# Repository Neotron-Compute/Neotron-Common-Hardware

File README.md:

# Neotron-Common-Hardware

Contains KiCad footprints and symbols shared across multiple Neotron projects. It also contains example schematics for circuits we expect to see on most Neotron boards.

## Components

### Audio Codec

* Texas Instruments TLV320AIC23B
  * I²S + I²C interface
  * Amplified 32mW headphone output and line out
  * Microphone in and line in
  * TSSOP-28 package (0.635mm pitch)
* Triple 3.5mm TRS jack (Kycon STX-4335-5BGP-S1)
  * Headphone Out (green)
  * Line In (blue)
  * Microphone In (pink)
* AC'97 Pin Header
  * Headphone Out
  * Microphone In
* Extra line-level output pin header (e.g. for additional RCA audio jacks - operates in addition to 3.5mm headphone jack output)
* Internal line-level input pin header (e.g. for CD-ROM audio - disabled when line-in 3.5mm jack in-use)

### Super VGA output

* 15-pin D-Sub VGA interface
* 18-bit (6-6-6) and 12-bit (4-4-4) RGB R2R DACs
  * Requires you to connect up a CPU that can generate digital parallel RGB video
* 3peak TPF133A or Texas Instruments THS7316 RGB video buffer
   * 36 MHz bandwidth - 1024x768@60Hz maximum
   * 6dB gain
   * Drives 75 ohm standard VGA interface
   * SOIC-8 package (1.27mm pitch)
* Texas Instruments TPD7S019 Sync/DDC level shifter and RGB EMC filter
   * SSOP-16 package (0.635mm pitch)

### RS232 Interface

* Tx, Rx, RTS and CTS signals
* 3.3V TTL on the MCU side
* Low-power ST ST3232C RS-232 level shifter (powered from single 3.3V rail)
* RS-232 signalling on a 9-pin D-Sub connector (or 10-pin IDC box header), wired DTE

### USB

* Four port USB 2.0 High Speed hub
* MaxLinear XR22404CG28 USB2.0 hub IC
  * SSOP-28 package (0.635mm pitch)
* Two USB 2.0 High Speed Type-A ports
* 8-pin PC case style USB pin-header (providing two USB 2.0 High Speed ports)
* Each port limited to 500mA with over-current protection

### Ethernet

* 10/100base-T Ethernet
* Microchip ENC424J600 Ethernet MAC/PHY with SPI connection to main CPU
  * TQFP-44 package (0.8mm pitch)
* Link and Activity LEDs

### Board Management Controller

Power-on Reset sequencing, soft shutdown, voltage monitoring and PS/2 interfacing is handled by a separate STM32F0 SoC.

* ST Micro STM32F0 (STM32F030K6T6) microcontroller
  * 32-bit Arm Cortex-M0+ Core
  * 3.3V I/O (5V tolerant)
  * 32 KiB Flash
  * 4 KiB SRAM
  * LQFP-32 package (0.8mm pitch)
* Controls two PS/2 ports
* Monitors 5V and 3.3V rails
* Controls system reset, soft-on and soft-off for main CPU
* Can the main 5V regulator on and off
* Runs from 3.3V stand-by regulator
* SPI interface (with dedicated IRQ line) with main CPU
* Secondary I²C bus which can be controlled over SPI

| Pin  | Name | Signal      | Function                                     |
| :--- | :--- | :---------- | :------------------------------------------- |
| 02   | PF0  | nBUTTON_PWR | Power Button Input (active low)              |
| 03   | PF1  | nBUTTON_RST | Reset Button Input (active low)              |
| 06   | PA0  | MON_3V3     | 3.3V rail monitor Input (1.65V nominal)      |
| 07   | PA1  | MON_5V      | 5.0V rail monitor Input (1.65V nominal)      |
| 08   | PA2  | nSYS_RESET  | Reset Output to reset the rest of the system |
| 09   | PA3  | DC_ON       | PSU Enable Output                            |
| 10   | PA4  | SPI1_NSS    | SPI Chip Select Input (active low)           |
| 11   | PA5  | SPI1_SCK    | SPI Clock Input                              |
| 12   | PA6  | SPI1_CIPO   | SPI Data Output                              |
| 13   | PA7  | SPI1_COPI   | SPI Data Input                               |
| 14   | PB0  | LED0        | PWM output for first Status LED              |
| 15   | PB1  | LED1        | PWM output for second Status LED             |
| 18   | PA8  | nHOST_IRQ   | Interrupt Output to the Host (active low)    |
| 19   | PA9  | USART1_TX   | UART Transmit Output                         |
| 20   | PA10 | USART1_RX   | UART Receive Input                           |
| 21   | PA11 | USART1_CTS  | UART Clear-to-Send Output                    |
| 22   | PA12 | USART1_RTS  | UART Ready-to-Receive Input                  |
| 23   | PA13 | SWDIO       | SWD Progamming Data Input                    |
| 24   | PA14 | SWCLK       | SWD Programming Clock Input                  |
| 25   | PA15 | PS2_CLK0    | Keyboard Clock Input                         |
| 26   | PB3  | PS2_CLK1    | Mouse Clock Input                            |
| 27   | PB4  | PS2_DAT0    | Keyboard Data Input                          |
| 28   | PB5  | PS2_DAT1    | Mouse Data Input                             |
| 29   | PB6  | I2C1_SCL    | I²C Clock                                    |
| 30   | PB7  | I2C1_SDA    | I²C Data                                     |

Note that in the above table, the UART signals labelled from the point of view of the BMC chip (i.e. UART_RX is an input to the BMC). The PS/2 signals are 5V open-collector, and so must be on 5V tolerant pins. Everything else runs at 3.3V.

This design should also be pin-compatible with the following SoCs (although the software may need recompiling with a different _Peripheral Access Crate_):

* STM32F031K6Tx
* STM32F042K4Tx
* STM32F042K6Tx
* STM32F051K4Tx
* STM32F051K6Tx
* STM32F051K8Tx
* STM32L071KBTx
* STM32L071KZTx
* STM32L072KZTx
* STM32L081KZTx
* STM32L082KZTx

Note that not all STM32 pins are 5V-tolerant, and as noted above, the PS/2 pins are 5V open-collector. You must therefore ensure that whichever part you pick has 5V-tolerant pins (marked `FT` or `FTt` in the datasheet) for the PS/2 signals. All of the parts above _should_ be OK, but they haven't been tested. Let us know if you try one!

### PS/2 Keyboard and Mouse

* Kycon two-port stacked 6-pin DIN sockets (Kycon KMDGX-6S/6S-S4N)
* Controlled via Board Management Controller

### Power Supply

* Unregulated 12V (8V to 28V) input fused with a PTC at 2A
* 3A 5.0V main regulator (DC-DC switch-mode regulator module)
  * Morsun K7805-3AR3
* 30mA 3.3V stand-by regulator (a micropower linear regulator)
* 1A 3.3V regulator (a high-power 1117 type linear regulator)
* Controlled by the Board Management Controller

### CPU Socket

The CPU can either be designed to solder direct to your particular motherboard design, or it can be fitted to a second PCB 'CPU card' which plugs into a socket on the motherboard. We have designed a special 80-pin socket pinout, which provides all the signals for required for the standard peripherals available in this design.

The socket is basically two 2x20 pin headers, placed 130 mil apart. This should give enough space to fit even a TQFP-176 microcontroller and some TSOP-54 SDRAM.

The pins are labelled in row.column fashion, i.e. 1.1 is top left, 1.20 is top right and 4.20 is bottom right.

```
 +----- Pin 1.1
 |
 v
+---------------------------------------+
|o o o o o o o o o o o o o o o o o o o o|
|o o o o o o o o o o o o o o o o o o o o|
+---------------------------------------+

+---------------------------------------+
|o o o o o o o o o o o o o o o o o o o o|
|o o o o o o o o o o o o o o o o o o o o|
+---------------------------------------+
                                       ^
                                       |
                         Pin 4.20 -----+
```

| Pin  | Function             |
| :--- | :------------------- |
| 1.1  | VGA_RED5             |
| 1.2  | VGA_RED4             |
| 1.3  | VGA_RED3             |
| 1.4  | VGA_RED2             |
| 1.5  | VGA_RED1             |
| 1.6  | VGA_RED0             |
| 1.7  | VGA_GREEN5           |
| 1.8  | VGA_GREEN4           |
| 1.9  | VGA_GREEN3           |
| 1.10 | VGA_GREEN2           |
| 1.11 | VGA_GREEN1           |
| 1.12 | VGA_GREEN0           |
| 1.13 | VGA_BLUE5            |
| 1.14 | VGA_BLUE4            |
| 1.15 | VGA_BLUE3            |
| 1.16 | VGA_BLUE2            |
| 1.17 | VGA_BLUE1            |
| 1.18 | VGA_BLUE0            |
| 1.19 | VGA_HSYNC            |
| 1.20 | VGA_VSYNC            |
| 2.1  | VGA_DDC_SDA          |
| 2.2  | VGA_DDC_SCL          |
| 2.3  | UART_RX              |
| 2.4  | UART_TX              |
| 2.7  | 3V3                  |
| 2.8  | 3V3                  |
| 2.9  | 3V3                  |
| 2.10 | GND                  |
| 2.11 | GND                  |
| 2.12 | GND                  |
| 2.13 | AUDIO_BCLK_TO_CODEC  |
| 2.14 | AUDIO_DAT_TO_CODEC   |
| 2.15 | AUDIO_LR_TO_CODEC    |
| 2.16 | AUDIO_DAT_FROM_CODEC |
| 2.17 | AUDIO_LR_FROM_CODEC  |
| 2.18 | USB_EN               |
| 2.19 | USB_D-               |
| 2.20 | USB_D+               |
| 3.1  | I2C_SDA              |
| 3.2  | I2C_SCL              |
| 3.3  | UART_CTS             |
| 3.4  | UART_RTS             |
| 3.7  | GND                  |
| 3.8  | GND                  |
| 3.9  | GND                  |
| 3.10 | 5V                   |
| 3.11 | 5V                   |
| 3.12 | 5V                   |
| 3.13 | ~SPI_CS7             |
| 3.14 | ~SPI_CS6             |
| 3.15 | ~SPI_CS5             |
| 3.16 | ~SPI_CS4             |
| 3.17 | ~SPI_CS3             |
| 3.18 | ~SPI_CS2             |
| 3.19 | ~SPI_CS1             |
| 3.20 | ~SPI_CS0             |
| 4.1  | ~SDMMC_CARD_DETECT   |
| 4.2  | ~SDMMC_WRITE_PROT    |
| 4.3  | SDMMC_DAT2           |
| 4.4  | SDMMC_DAT3           |
| 4.5  | SDMMC_CMD            |
| 4.6  | SDMMC_CLK            |
| 4.7  | SDMMC_DAT0           |
| 4.8  | SDMMC_DAT1           |
| 4.9  | SPI_COPI             |
| 4.10 | SPI_CIPO             |
| 4.11 | SPI_CLK              |
| 4.12 | ~RESET               |
| 4.13 | ~IRQ7                |
| 4.14 | ~IRQ6                |
| 4.15 | ~IRQ5                |
| 4.16 | ~IRQ4                |
| 4.17 | ~IRQ3                |
| 4.18 | ~IRQ2                |
| 4.19 | ~IRQ1                |
| 4.20 | ~IRQ0                |

## Expansion

The (up-to) seven expansion sockets allow you to add on I²C or SPI based devices at a later date. Each provides a single chip-select and a single IRQ line - the motherboard design should ensure each socket gets a unique signal for each of these. Each expansion device should also contain a AT24C256 or similar EEPROM device. To allow these EEPROM devices to be scanned, each slot also contains three `EEPROM_ADDRESS` pins, tied to Vcc or GND in a unique combination. These should be connected through to the EEPROM address lines on your AT24C256, thus ensuring that each expansion card has its EEPROM at a unique address - 0x50 on Slot 0 through to a maximum possible 0x57 for Slot 7. Where your board has on-board devices, you should fit an AT24C256 EEPROM for each device so that the on-board devices can be discovered, exactly as if they were on an expansion card.

The expansion slot is a simple 2x10 header. We suggest the use of a TE card-edge connector, but you could equally use two 1x10 pin-headers if desired.

The pin functions are:

```
     SPI_COPI   1    2   GND
     SPI_CIPO   3    4   GND
      SPI_CLK   5    6   GND
      ~SPI_CS   7    8   ~IRQ
      I2C_SDA   9   10   I2C_SCL
 EEPROM_ADDR0   11  12   EEPROM_ADDR1
 EEPROM_ADDR2   13  14   ~RESET
           5V   15  16   5V
          3V3   17  18   3V3
          GND   19  20   GND
```

There are symbols and footprints for the mainboard side (card-edge socket, supplies power), and the expansion card side (golden-finger edge connector, receives power).

## Expansion Ideas

Why not design and build your own expansion card? You could try designing:

* A dual Atari/SEGA 9-pin Joypad Interface
* A Mikro Eletronika Click adaptor, allow many of the range of [Click boards](https://www.mikroe.com/click) to be fitted
* A Wi-Fi/Bluetooth card, using an Espressif ESP32
* A second processor card - perhaps with a RISC-V microcontroller, or classic Zilog Z80
* An OPL2 or OPL3 based FM synthesiser card
* An ISA adaptor card (taking an ISA card at right-angles, i.e. parallel to the base board) - a simple microcontroller should be able to bit-bang the ISA bus at 8 MHz and offer an SPI peripheral interface to the Neotron Expansion Slot
* An IDE interface card, allowing 40-pin IDE Hard Disk Drives and CD-ROM drives to be used - this will be quite similar to an ISA bus adaptor
* A floppy drive controller card - either using an eSPI Super I/O chip, or connecting a legacy ISA bus floppy controller as per the ISA adaptor
* A video card for a second monitor output, perhaps based on the CPLD used in the [VGAtonic](https://hackaday.io/project/6309-vga-graphics-over-spi-and-serial-vgatonic)

## Changelog

See [CHANGELOG.md](./CHANGELOG.md) for a list of detailed changes.

## Git Setup

We recommend you have the following Git config set:

```
$ git config --global filter.kicad_project.clean "sed -E 's/^update=.*$/update=Date/'"
$ git config --global filter.kicad_project.smudge cat
$ git config --global filter.kicad_sch.clean "sed -E 's/#(PWR|FLG)[0-9]+/#\1?/'"
$ git config --global filter.kicad_sch.smudge cat
```

See https://jnavila.github.io/plotkicadsch/ for details.

## Automated Builds

This project treats a PCB like embedded firmware:

* The *source files* are the KiCAD 7 files (in `./Kicad`)
* The *compiler* is KiCAD 7, plus various automation plug-ins (like KiBom)
* The *build system* is [KiBot](https://github.com/INTI-CMNB/KiBot)
* The *build outputs* are PDF versions of the schematic and the PCB, plus various zipped Gerber and Drill files.

We do not check *build outputs* into this repository - *ever*. Instead, we run a Github Action which uses KiBot to generate our outputs. On a regular Pull Request, the *build outputs* are stored as *artefacts* against the particular Github Action run. When a new version is tagged, the *build outputs* are stored as files against a [Github Release](https://github.com/Neotron-Compute/Neotron-Common-Hardware/releases).

Of course, the PCB in this project isn't useful by itself - it's a starting point for your project. You should probably include this repo as a Git Submodule, and add the symbol library and footprint library to your own KiCAD project.

You can build locally using the KiBot docker container:

```console
~/Neotron-Common-Hardware $ docker run --rm -ti -v $(pwd):/work setsoft/kicad_auto:ki7
root@12345678:/# cd /work/Kicad
root@12345678:/work/Kicad# kibot -c docs.kibot.yml -e Neotron-Common-Hardware.kicad_sch -b Neotron-Common-Hardware.kicad_pcb -d docs
```

This will build everything and put it in the `./Kicad/docs` directory.

## Licence

This schematic and PCB design is Copyright (c) The Neotron Developers.

This work is licensed under a [Creative Commons Attribution-ShareAlike 4.0 International License](http://creativecommons.org/licenses/by-sa/4.0/).

## Contribution Agreement

Unless you explicitly state otherwise, any contribution intentionally submitted for inclusion in the work by you, as defined in the Apache-2.0 license, shall be licensed as above, without any additional terms or conditions.

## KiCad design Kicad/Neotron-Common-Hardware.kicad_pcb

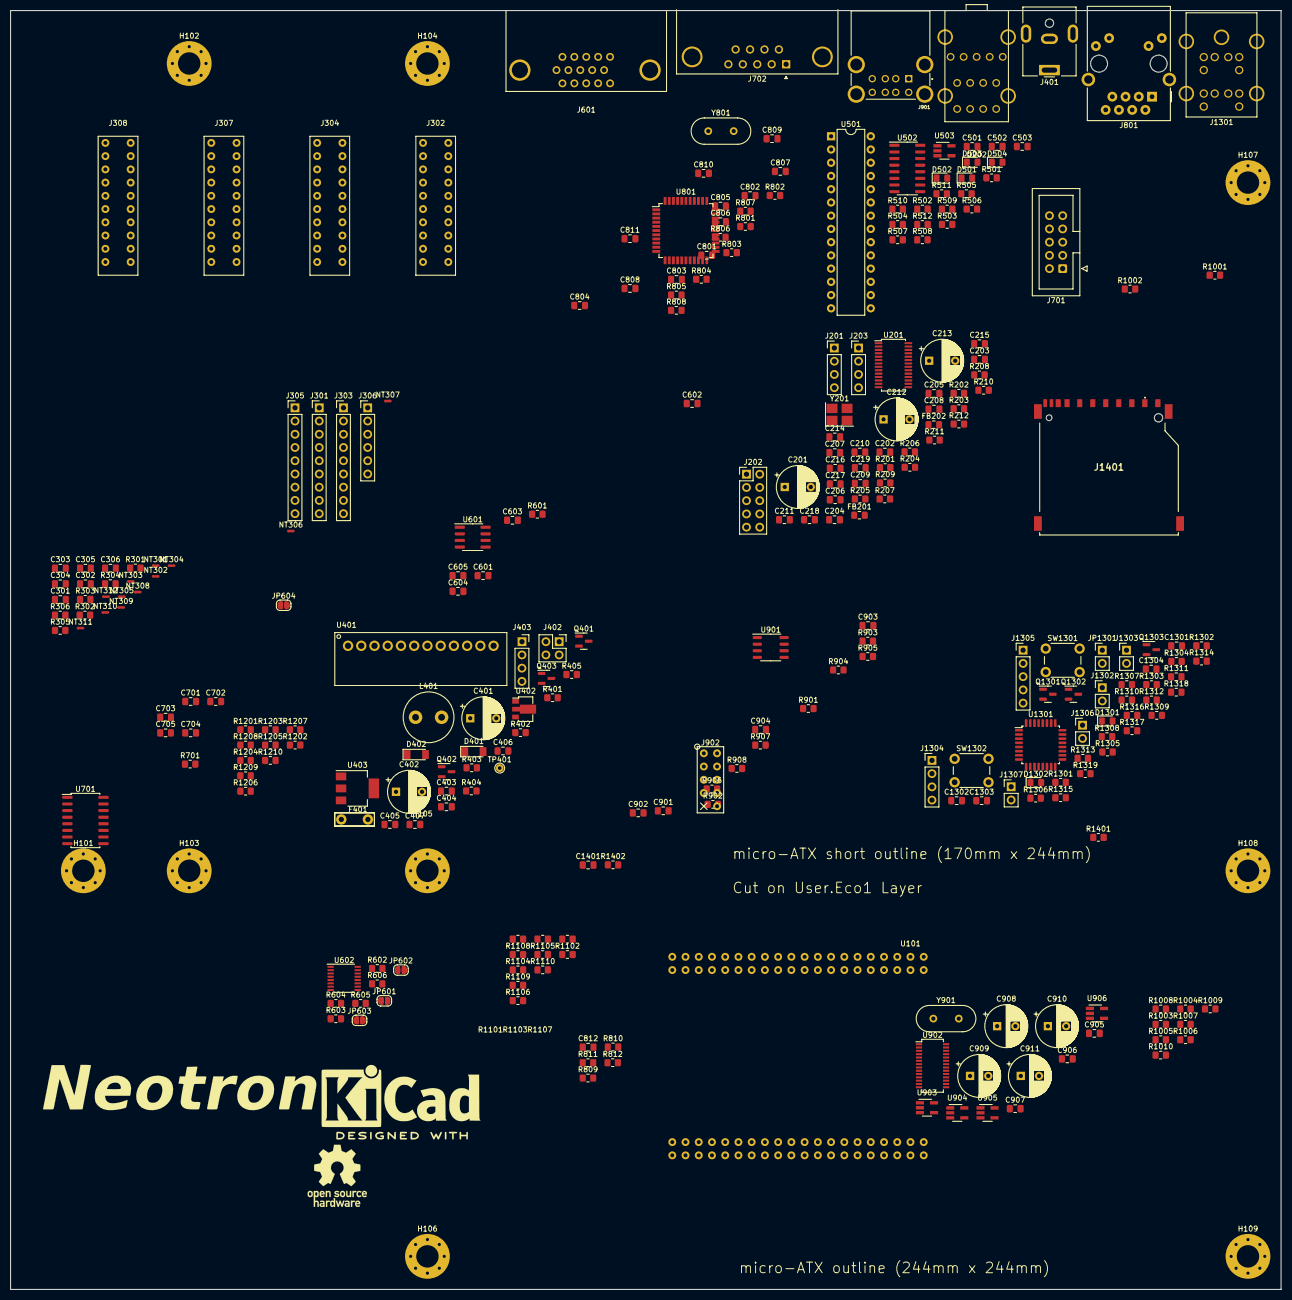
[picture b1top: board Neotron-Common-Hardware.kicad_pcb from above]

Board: 4 copper layers, 243.8 x 245.5 mm, 287 parts (0 on the bottom side), 218 nets, no tracks yet.

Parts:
C201, C212, C213, C401, C402: 100u; CP_Radial_D8.0mm_P5.00mm
C202, C205, C206, C207, C209, C404, C405, C502, C503, C601, C603, C604, C605, C808, C1301, C1302, C1304, C1401: 10u; C_0805_2012Metric_Pad1.18x1.45mm_HandSolder
C203, C204: 22p; C_0805_2012Metric_Pad1.18x1.45mm_HandSolder
C208, C701, C702, C703, C704, C705, C801, C802, C803, C804, C805, C902, C904, C906: 100n; C_0805_2012Metric_Pad1.18x1.45mm_HandSolder
C210, C211, C214, C215, C218: 1u; C_0805_2012Metric_Pad1.18x1.45mm_HandSolder
C216, C217, C219: 47p; C_0805_2012Metric_Pad1.18x1.45mm_HandSolder
C301, C302, C303, C304, C305, C306, C501: DNF; C_0805_2012Metric_Pad1.18x1.45mm_HandSolder
C403, C406, C407: 22u; C_0805_2012Metric_Pad1.18x1.45mm_HandSolder
C602: 220n; C_0805_2012Metric_Pad1.18x1.45mm_HandSolder
C806, C807: 1n; C_0805_2012Metric_Pad1.18x1.45mm_HandSolder
C809, C810, C901, C903: 12p; C_0805_2012Metric_Pad1.18x1.45mm_HandSolder
C811, C812, C1303: 10n; C_0805_2012Metric_Pad1.18x1.45mm_HandSolder
C905, C907: 4.7u; C_0805_2012Metric_Pad1.18x1.45mm_HandSolder
C908, C909, C910, C911: 120u; CP_Radial_D8.0mm_P3.50mm
D401, D402: ZMM5V6; D_MiniMELF
D501, D502, D503, D504, D1301, D1302: LED; LED_0805_2012Metric_Pad1.15x1.40mm_HandSolder
F401: 32V 2A PTC; Bel Fuse 0ZRS0200FF
FB201, FB202: 330R@100MHz; L_0805_2012Metric_Pad1.15x1.40mm_HandSolder
H101, H102, H103, H104, H105, H106, H107, H108, H109: MountingHole_Pad; MountingHole_4.3mm_M4_Pad_Via
J201, J203, J1304: Conn_01x04; PinHeader_1x04_P2.54mm_Vertical
J202: Conn_02x05; PinHeader_2x05_P2.54mm_Vertical
J301, J303, J305: Conn_01x09; PinHeader_1x09_P2.54mm_Vertical
J302, J304, J307, J308: Neotron-Expansion-Slot
J306: Conn_01x06; PinHeader_1x06_P2.54mm_Vertical
J401: Jack 2.1mm 6.3mm; BarrelJack_CUI_PJ-063AH_Horizontal
J402: Conn_02x02S; PinSocket_2x02_P2.54mm_Vertical
J403: Conn_01x04S; PinSocket_1x04_P2.54mm_Vertical
J601: DE15HD; Amphenol_ICD15S13E4GV00LF
J701: Conn_02x05; IDC-Header_2x05_P2.54mm_Vertical
J702: DB9_Male_MountingHoles; DSUB-9_Male_Horizontal_P2.77x2.84mm_EdgePinOffset7.70mm_Hou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
J801: RJ45 MagJack; RJ45_Amphenol_RJMG1BD3B8K1ANR
J901: USB Ports External; CUI_UJ2-ADH-1-TH
J902: USB Ports Internal; USB_Header
J1301: Double-mini-DIN-6; Double_mini-DIN_6
J1302, J1303, J1306, J1307: Conn_01x02; PinHeader_1x02_P2.54mm_Vertical
J1305: Conn_01x05; PinHeader_1x05_P2.54mm_Vertical
J1401: SD_Card; Amphenol_GSD090012SEU
JP601, JP602, JP603, JP604: Bridge; SolderJumper-2_P1.3mm_Open_RoundedPad1.0x1.5mm
JP1301: Jumper; PinHeader_1x02_P2.54mm_Vertical
L401: 22uH; L_Radial_D9.5mm_P5.00mm_Fastron_07HVP
LOGO101: Neotron Logo; logo
LOGO102: Kicad Logo; KiCad-Logo2_12mm_SilkScreen
LOGO103: OSHW Logo; OSHW-Logo_11.4x12mm_SilkScreen
NT301, NT302, NT303, NT304, NT305, NT306, NT307, NT308, NT309, NT310, NT311, NT312: NetTie_2; NetTie-2_SMD_Pad0.5mm
Q401, Q1301: SS8050; SOT-23
Q402: AO3401A; SOT-23
Q403: SS8550; SOT-23
Q1302, Q1303: 2N7002; SOT-23
R201, R202, R204, R301, R302, R303, R304, R305, R306, R501: 0R; R_0805_2012Metric_Pad1.20x1.40mm_HandSolder
R203, R605, R606, R1001, R1002, R1004, R1006, R1008, R1101, R1102, R1104, R1106, R1108, R1201, R1202, R1204, R1206, R1208: 2k; R_0805_2012Metric_Pad1.20x1.40mm_HandSolder
R205, R206, R208, R209, R801: 100k; R_0805_2012Metric_Pad1.20x1.40mm_HandSolder
R207, R210, R211, R212: 4k7; R_0805_2012Metric_Pad1.20x1.40mm_HandSolder
R401, R402, R403, R404, R502, R504, R506, R508, R510, R511, R512, R901, R902, R903, R904, R905, R907, R908, R1305, R1308, R1314, R1315, R1317, R1318, R1319, R1401, R1402: 10k; R_0805_2012Metric_Pad1.20x1.40mm_HandSolder
R405, R503, R505, R507, R509, R1003, R1005, R1007, R1009, R1103, R1105, R1107, R1109, R1203, R1205, R1207, R1209, R1301, R1302, R1303, R1304, R1306, R1309, R1312: 1k; R_0805_2012Metric_Pad1.20x1.40mm_HandSolder
R601, R602, R603: 75; R_0805_2012Metric_Pad1.20x1.40mm_HandSolder
R604, R701, R812: DNF; R_0805_2012Metric_Pad1.20x1.40mm_HandSolder
R802: 12k4; R_0805_2012Metric_Pad1.20x1.40mm_HandSolder
R803: 1M; R_0805_2012Metric_Pad1.20x1.40mm_HandSolder
R804, R805, R806, R807: 49R9; R_0805_2012Metric_Pad1.20x1.40mm_HandSolder
R808, R809: 10R; R_0805_2012Metric_Pad1.20x1.40mm_HandSolder
R810, R811: 180R; R_0805_2012Metric_Pad1.20x1.40mm_HandSolder
R906: 2k7; R_0805_2012Metric_Pad1.20x1.40mm_HandSolder
R1010, R1110, R1210, R1310, R1311, R1313, R1316: 300; R_0805_2012Metric_Pad1.20x1.40mm_HandSolder
R1307: 33R; R_0805_2012Metric_Pad1.20x1.40mm_HandSolder
SW1301, SW1302: SW_Push; SW_PUSH_6mm
TP401: PTH; TestPoint_THTPad_D1.5mm_Drill0.7mm
U101: Neotron-CPU; Neotron_CPU_Socket
U201: TLV320AIC23BPW; TSSOP-28_4.4x9.7mm_P0.65mm
U202: STX-4335-5BGP-S1
U401: DC-DC Module; K78xx-3AR3
U402: HT75xx-1-SOT89; SOT-89-3
U403: AMS1117-3.3; SOT-223-3_TabPin2
U501: MCP23S17_SP; DIP-28_W7.62mm
U502: 74HC138; SOIC-16_3.9x9.9mm_P1.27mm
U503: 74AHC1G04; SOT-23-5_HandSoldering
U601: THS7316; SOIC-8_3.9x4.9mm_P1.27mm
U602: TPD7S019; SSOP-16_3.9x4.9mm_P0.635mm
U701: ST3232CDR; SO-16_5.3x10.2mm_P1.27mm
U801: ENC424J600; TQFP-44_10x10mm_P0.8mm
U901: AP2501; SO-8_3.9x4.9mm_P1.27mm
U902: XR22404CG28; SSOP-28_3.9x9.9mm_P0.635mm
U903, U904, U905, U906: MIC2005A-2YM5; SOT-23-5_HandSoldering
U1301: STM32F030K6T6; LQFP-32_7x7mm_P0.8mm
Y201: 12M 20pF; Crystal_SMD_3225-4Pin_3.2x2.5mm_HandSoldering
Y801: 25M; Crystal_HC49-4H_Vertical
Y901: 12M; Crystal_HC49-4H_Vertical

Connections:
+3.3VP: C405.2, C1301.2, C1302.2, C1303.1, C1304.2, J1305.5, JP1301.1 (A), U402.3 (VOUT), U1301.1 (VDD), U1301.5 (VDDA), U1301.17 (VDD)
+3V3: C407.1, C502.1, C503.1, C601.1, C605.2, C701.2, C801.1, C802.1, C803.1, C804.1, C805.1, C806.1, C807.1, C1401.2, FB201.2, FB202.2, J301.8, J302.17 (3V3), J302.18 (3V3), J304.17 (3V3), J304.18 (3V3), J307.17 (3V3), J307.18 (3V3), J308.17 (3V3), J308.18 (3V3), J403.1, J1401.4 (VDD), NT302.2, NT304.2, NT305.2, NT309.2, NT310.2, NT312.2, R502.1, R503.1, R504.1, R505.1, R506.1, R507.1, R508.1, R509.1, R510.1, R512.1, R801.1, R804.2, R805.1, R806.2, R807.1, R808.1, R809.1, R901.1, R908.1, R1314.1, R1401.2, R1402.1, U101.2.7 (3V3), U101.2.8 (3V3), U101.2.9 (3V3), U403.2 (VO), U501.9 (VDD), U502.16 (VCC), U503.5 (VCC), U601.4 (Vcc), U602.7 (VCC_DDC), U701.16 (VCC), U801.4 (VDDOSC), U801.12 (VDDPLL), U801.15 (VDDRX), U801.18 (VDDTX), U801.44 (VDD)
+5V: C403.1, C406.1, C603.2, C604.2, C902.1, J202.7, J301.9, J302.15 (5V), J302.16 (5V), J304.15 (5V), J304.16 (5V), J307.15 (5V), J307.16 (5V), J308.15 (5V), J308.16 (5V), J403.4, J601.9, J1301.4, J1301.10, R605.1, R606.1, R1301.1, R1302.1, R1303.1, R1304.1, R1307.2, R1310.1, R1311.1, R1313.1, R1316.1, R1317.1, U101.3.10 (5V), U101.3.11 (5V), U101.3.12 (5V), U401.4 (Vo), U403.3 (VI), U602.1 (VCC_SYNC), U602.2 (VCC_VIDEO), U901.2 (IN), U901.3 (IN)
/Audio/3V3_ANALOG: C201.1, C205.1, C207.1, FB201.1, U201.8 (HPVDD), U201.14 (AVDD)
/Audio/3V3_DIGITAL: C202.1, C206.1, FB202.1, U201.1 (BVDD), U201.27 (DVDD)
/Audio/CDInL: J201.1, U202.34 (BlueTipOut)
/Audio/CDInR: J201.4, U202.33 (BlueRingOut)
/Audio/FrontHPL: C212.2, J202.9, R209.2
/Audio/FrontHPR: C213.2, J202.5, R206.1
/Audio/FrontMicAudio: J202.1, U202.4 (PinkTipOut)
/Audio/FrontMicBias: J202.3, U202.3 (PinkRingOut)
/Audio/LHpOut: C212.1, U201.9 (LHPOUT)
/Audio/LLineIn: C214.2, U201.20 (LLINEIN)
/Audio/LOut: C210.1, U201.12 (LOUT)
/Audio/LineOutL: C210.2, J203.1, R208.2
/Audio/LineOutR: C211.1, J203.4, R205.1
/Audio/MicBias: R203.2, U201.17 (MICBIAS)
/Audio/MicIn: R204.1, U201.18 (MICIN)
/Audio/RHpOut: C213.1, U201.10 (RHPOUT)
/Audio/RLineIn: C215.2, U201.19 (RLINEIN)
/Audio/ROut: C211.2, U201.13 (ROUT)
/Audio/RearHPL: J202.10, U202.25 (LimeTip)
/Audio/RearHPR: J202.6, U202.22 (LimeRing)
/Audio/RearInL: R211.1, U202.35 (BlueTip)
/Audio/RearInR: R212.1, U202.32 (BlueRing)
/Audio/RearMicAudio: C218.1, C219.2, U202.5 (PinkTip)
/Audio/RearMicBias: R203.1, U202.2 (PinkRing)
/Audio/VMID: C208.1, C209.1, U201.16 (VMID)
/Ethernet/~IRQ: R801.2, U801.24 (~INT/SPISEL)
/Expansion Slots/BMC/BUZZER: R1306.1, U1301.15 (PB1)
/Expansion Slots/BMC/LED0: D1302.2 (A), Q1303.1 (G), U1301.14 (PB0)
/Expansion Slots/BMC/MON_3V3: R1314.2, R1315.1, U1301.6 (PA0)
/Expansion Slots/BMC/MON_5V: R1318.2, R1319.1, U1301.7 (PA1)
/Expansion Slots/BMC/PS2_CLK0: J1301.5, R1301.2, U1301.25 (PA15)
/Expansion Slots/BMC/PS2_CLK1: J1301.11, R1303.2, U1301.26 (PB3)
/Expansion Slots/BMC/PS2_DAT0: J1301.1, R1302.2, U1301.27 (PB4)
/Expansion Slots/BMC/PS2_DAT1: J1301.7, R1304.2, U1301.28 (PB5)
/Expansion Slots/BMC/SPK_N: J1304.4, Q1301.3 (C)
/Expansion Slots/BMC/SPK_P: J1304.1, R1307.1
/Expansion Slots/BMC/SWCLK: J1305.4, U1301.24 (PA14)
/Expansion Slots/BMC/SWDIO: J1305.3, U1301.23 (PA13)
/Expansion Slots/BMC/~BMC_RST: J1305.2, U1301.4 (NRST)
/Expansion Slots/BMC/~BUTTON_PWR: J1302.1, SW1301.2, U1301.2 (PF0)
/Expansion Slots/BMC/~BUTTON_RST: J1303.1, SW1302.2, U1301.3 (PF1)
/Expansion Slots/DC_ON: R401.2, U1301.9 (PA3)
/Expansion Slots/FTDI_BRN: J306.2, U1301.22 (PA12)
/Expansion Slots/FTDI_GRN: J306.6, U1301.21 (PA11)
/Expansion Slots/FTDI_ORA: J306.4, U1301.20 (PA10)
/Expansion Slots/FTDI_YEL: J306.5, U1301.19 (PA9)
/Expansion Slots/HDD_LED: D1301.2 (A), Q1302.1 (G)
/Expansion Slots/PICO_SCL: J301.3, J302.10 (I2C_SCL), J304.10 (I2C_SCL), J307.10 (I2C_SCL), J308.10 (I2C_SCL)
/Expansion Slots/PICO_SDA: J301.2, J302.9 (I2C_SDA), J304.9 (I2C_SDA), J307.9 (I2C_SDA), J308.9 (I2C_SDA)
/Expansion Slots/SD Card/~WRITE_PROTECT: J1401.11 (WRITE_PROTECT), R1402.2
/Expansion Slots/SPI_CIPO: C301.1, C302.1, C303.1, C304.1, C305.1, C306.1, J301.7, R301.2, R302.2, R303.2, R304.2, R305.2, R306.2
/Expansion Slots/SPI_CIPO_S0: R302.1, U1301.12 (PA6)
/Expansion Slots/SPI_CIPO_S1: J1401.7 (DAT0), R306.1
/Expansion Slots/SPI_CIPO_S2: J302.3 (SPI_CIPO), R301.1
/Expansion Slots/SPI_CIPO_S3: J304.3 (SPI_CIPO), R303.1
/Expansion Slots/SPI_CIPO_S4: J307.3 (SPI_CIPO), R304.1
/Expansion Slots/SPI_CIPO_S5: J308.3 (SPI_CIPO), R305.1
/Expansion Slots/SPI_CLK: J301.5, J302.5 (SPI_CLK), J304.5 (SPI_CLK), J307.5 (SPI_CLK), J308.5 (SPI_CLK), J1401.5 (CLK), U1301.11 (PA5)
/Expansion Slots/SPI_COPI: J301.6, J302.1 (SPI_COPI), J304.1 (SPI_COPI), J307.1 (SPI_COPI), J308.1 (SPI_COPI), J1401.2 (CMD), U1301.13 (PA7)
/Expansion Slots/~CS0: J305.2, U502.15 (O0), U1301.10 (PA4)
/Expansion Slots/~CS1: J305.3, J1401.1 (CD/DAT3), U502.14 (O1)
/Expansion Slots/~CS2: J302.7 (~SPI_CS), J305.4, U502.13 (O2)
/Expansion Slots/~CS3: J304.7 (~SPI_CS), J305.5, U502.12 (O3)
/Expansion Slots/~CS4: J305.6, J307.7 (~SPI_CS), U502.11 (O4)
/Expansion Slots/~CS5: J305.7, J308.7 (~SPI_CS), U502.10 (O5)
/Expansion Slots/~CS6: J305.8, U502.9 (O6)
/Expansion Slots/~CS7: J305.9, U502.7 (O7)
/Expansion Slots/~IRQ0: J303.2, U501.1 (GPB0), U1301.18 (PA8)
/Expansion Slots/~IRQ1: J303.3, J1401.10 (CARD_DETECT), R1401.1, U501.2 (GPB1)
/Expansion Slots/~IRQ2: J302.8 (~IRQ), J303.4, U501.3 (GPB2)
/Expansion Slots/~IRQ3: J303.5, J304.8 (~IRQ), U501.4 (GPB3)
/Expansion Slots/~IRQ4: J303.6, J307.8 (~IRQ), U501.5 (GPB4)
/Expansion Slots/~IRQ5: J303.7, J308.8 (~IRQ), U501.6 (GPB5)
/Expansion Slots/~IRQ6: J303.8, U501.7 (GPB6)
/Expansion Slots/~IRQ7: J303.9, U501.8 (GPB7)
/Expansion Slots/~RESET: J301.4, J302.14 (~RESET), J304.14 (~RESET), J307.14 (~RESET), J308.14 (~RESET), R1308.1, U1301.8 (PA2)
/IO Expansion/CS_SEL0: R502.2, U501.21 (GPA0), U502.1 (A0)
/IO Expansion/CS_SEL1: R504.2, U501.22 (GPA1), U502.2 (A1)
/IO Expansion/CS_SEL2: R506.2, U501.23 (GPA2), U502.3 (A2)
/IO Expansion/E2: R511.1, U502.5 (E2)
/IO Expansion/E3: R510.2, U502.6 (E3)
/IO Expansion/SPI_CIPO: C501.1, R501.2
/IO Expansion/~LED0: R512.2, U501.24 (GPA3), U503.2
/IO Expansion/~LED1: D501.1 (K), U501.25 (GPA4)
/IO Expansion/~LED2: D502.1 (K), U501.26 (GPA5)
/IO Expansion/~LED3: D503.1 (K), U501.27 (GPA6)
/IO Expansion/~LED4: D504.1 (K), U501.28 (GPA7)
/IO Expansion/~OUTPUT_EN: R508.2, U502.4 (E1)
/Power Supply/PSU_CTRL: D402.1 (K), R405.1, U401.1 (Ctrl)
/Serial/RS232_CTS_IN: J701.8, J702.8, U701.8 (R2IN)
/Serial/RS232_RTS_OUT: J701.7, J702.7, U701.7 (T2OUT)
/Serial/RS232_RX_IN: J701.2, J702.2, U701.13 (R1IN)
/Serial/RS232_TX_OUT: J701.3, J702.3, U701.14 (T1OUT)
/USB/USBD1+: J901.2 (D-), U902.11 (D1+)
/USB/USBD1-: J901.3 (D+), U902.10 (D1-)
/USB/USBD2+: J901.6 (D-), U902.9 (D2+)
/USB/USBD2-: J901.7 (D+), U902.8 (D2-)
/USB/USBD3+: J902.2 (D-), U902.7 (D3+)
/USB/USBD3-: J902.3 (D+), U902.6 (D3-)
/USB/USBD4+: J902.6 (D-), U902.5 (D4+)
/USB/USBD4-: J902.7 (D+), U902.4 (D4-)
/USB/USB_3V3: C904.1, C905.1, R902.1, R903.1, R904.1, R905.1, U902.21 (VCC33)
/USB/USB_5V: C906.1, C907.1, U901.6 (OUT), U901.7 (OUT), U902.20 (VCC5), U903.1 (VIN), U904.1 (VIN), U905.1 (VIN), U906.1 (VIN)
/USB/~ENABLE: R901.2, U901.4 (~EN)
/Video/BLUE_ANA: R1209.1, R1210.1, U601.3 (CH3_IN)
/Video/DDC_SCL: JP603.1 (A), U602.11 (DDC_IN2)
/Video/DDC_SDA: JP604.1 (A), U602.10 (DDC_IN1)
/Video/GREEN_ANA: R1109.1, R1110.1, U601.2 (CH2_IN)
/Video/HSYNC: JP601.1 (A), U602.15 (SYNC_IN2)
/Video/RED_ANA: R1009.1, R1010.1, U601.1 (CH1_IN)
/Video/VGA_BLU: J601.3, R603.1, U602.3 (VIDEO1)
/Video/VGA_DDC_SCL: J601.15, JP603.2 (B), R606.2, U602.12 (DDC_OUT2)
/Video/VGA_DDC_SDA: J601.12, JP604.2 (B), R605.2, U602.9 (DDC_OUT1)
/Video/VGA_GRN: J601.2, R602.1, U602.4 (VIDEO2)
/Video/VGA_HSYNC_BUF: J601.13, JP601.2 (B), U602.16 (SYNC_OUT2)
/Video/VGA_RED: J601.1, R601.1, U602.5 (VIDEO3)
/Video/VGA_VSYNC_BUF: J601.14, JP602.2 (B), U602.14 (SYNC_OUT1)
/Video/VSYNC: JP602.1 (A), U602.13 (SYNC_IN1)
GND: C201.2, C202.2, C203.1, C204.2, C205.2, C206.2, C207.2, C208.2, C209.2, C216.1, C217.1, C219.1, C301.2, C302.2, C303.2, C304.2, C305.2, C306.2, C401.2, C402.2, C403.2, C404.1, C405.1, C406.2, C407.2, C501.2, C502.2, C503.2, C601.2, C602.1, C603.1, C604.1, C605.1, C701.1, C704.1, C705.1, C801.2, C802.2, C803.2, C804.2, C805.2, C806.2, C807.2, C808.2, C809.2, C810.2, C811.2, C812.2, C901.2, C902.2, C903.2, C904.2, C905.2, C906.2, C907.2, C908.2, C909.2, C910.2, C911.2, C1301.1, C1302.1, C1303.2, C1304.1, C1401.1, D402.2 (A), H101.1, H102.1, H103.1, H104.1, H105.1, H106.1, H107.1, H108.1, H109.1, J201.2, J201.3, J202.2, J202.4, J203.2, J203.3, J301.1, J302.2 (GND), J302.4 (GND), J302.6 (GND), J302.19 (GND), J302.20 (GND), J303.1, J304.2 (GND), J304.4 (GND), J304.6 (GND), J304.19 (GND), J304.20 (GND), J305.1, J306.1, J307.2 (GND), J307.4 (GND), J307.6 (GND), J307.19 (GND), J307.20 (GND), J308.2 (GND), J308.4 (GND), J308.6 (GND), J308.19 (GND), J308.20 (GND), J401.2, J402.1, J402.2, J403.2, J403.3, J601.5, J601.6, J601.7, J601.8, J601.10, J701.5, J702.5, J801.L2 (LEDY_K), J801.L3 (LEDG_K), J801.R8 (GND), J901.4 (GND), J901.8 (GND), J901.9 (Shield), J902.4 (GND), J902.8 (GND), J902.9 (Shield), J1301.3, J1301.9, J1302.2, J1303.2, J1305.1, J1401.3 (VSS), J1401.6 (VSS), J1401.12 (SHELL1), J1401.13 (SHELL2), NT301.2, NT303.2, NT306.2, NT307.2, NT308.2, NT311.2, Q401.2 (E), Q1301.2 (E), Q1302.2 (S), Q1303.2 (S), R201.1, R202.1, R205.2, R206.2, R207.2, R208.1, R209.1, R210.1, R403.2, R404.2, R511.2, R604.1, R701.2, R802.2, R812.2, R906.2, R907.2, R1002.2, R1010.2, R1102.2, R1110.2, R1202.2, R1210.2, R1305.2, R1308.2, R1309.2, R1312.2, R1315.2, R1319.2, SW1301.1, SW1302.1, U101.2.10 (GND), U101.2.11 (GND), U101.2.12 (GND), U101.3.7 (GND), U101.3.8 (GND), U101.3.9 (GND), U201.11 (HPGND), U201.15 (AGND), U201.28 (DGND), U202.1 (Sleeve), U401.3 (GND), U402.1 (GND), U403.1 (GND), U501.10 (VSS), U501.15 (A0), U501.16 (A1), U501.17 (A2), U502.8 (GND), U503.3 (GND), U601.5 (GND), U602.6 (GND), U701.15 (GND), U801.1 (VSSOSC), U801.13 (VSSPLL), U801.14 (VSSRX), U801.19 (VSSTX), U801.22 (VSSTX), U801.33 (VSS), U801.42 (VSS), U901.1 (GND), U902.1 (GND), U903.2 (GND), U904.2 (GND), U905.2 (GND), U906.2 (GND), U1301.16 (VSS), U1301.32 (VSS), Y201.2, Y201.4
unnamed: C203.2, U201.26 (XTO), Y201.3
unnamed: C204.1, U201.25 (XTI/MCK), Y201.1
unnamed: C214.1, C217.2, R210.2, R211.2
unnamed: C215.1, C216.2, R207.1, R212.2
unnamed: C218.2, R204.2
unnamed: C401.1, D401.1 (K), L401.1, Q402.2 (S), TP401.1
unnamed: C602.2, U602.8 (BYP)
unnamed: C702.1, U701.3 (C1-)
unnamed: C702.2, U701.1 (C1+)
unnamed: C703.1, U701.4 (C2+)
unnamed: C703.2, U701.5 (C2-)
unnamed: C704.2, U701.2 (VS+)
unnamed: C705.2, U701.6 (VS-)
unnamed: C808.1, U801.43 (VCAP)
unnamed: C809.1, R803.2, Y801.1
unnamed: C810.1, U801.3 (OSC1), Y801.2
unnamed: C811.1, J801.R4 (TCT), R808.2
unnamed: C812.1, J801.R5 (RCT), R809.2
unnamed: C901.1, U902.2 (XTALOUT), Y901.2
unnamed: C903.1, U902.3 (XTALIN), Y901.1
unnamed: C908.1, J901.1 (VBUS), U903.5 (VOUT)
unnamed: C909.1, J901.5 (VBUS), U904.5 (VOUT)
unnamed: C910.1, J902.1 (VBUS), U905.5 (VOUT)
unnamed: C911.1, J902.5 (VBUS), U906.5 (VOUT)
unnamed: D401.2 (A), Q402.1 (G), R403.1
unnamed: D501.2 (A), R503.2
unnamed: D502.2 (A), R505.2
unnamed: D503.2 (A), R507.2
unnamed: D504.2 (A), R509.2
unnamed: D1301.1 (K), R1309.1
unnamed: D1302.1 (K), R1312.1
unnamed: F401.1, Q402.3 (D)
unnamed: F401.2, J401.1, J402.3, J402.4
unnamed: J302.11 (EEPROM_ADDR0), NT301.1
unnamed: J302.12 (EEPROM_ADDR1), NT302.1
unnamed: J302.13 (EEPROM_ADDR2), NT303.1
unnamed: J304.11 (EEPROM_ADDR0), NT304.1
unnamed: J304.12 (EEPROM_ADDR1), NT305.1
unnamed: J304.13 (EEPROM_ADDR2), NT306.1
unnamed: J307.11 (EEPROM_ADDR0), NT307.1
unnamed: J307.12 (EEPROM_ADDR1), NT308.1
unnamed: J307.13 (EEPROM_ADDR2), NT309.1
unnamed: J308.11 (EEPROM_ADDR0), NT310.1
unnamed: J308.12 (EEPROM_ADDR1), NT311.1
unnamed: J308.13 (EEPROM_ADDR2), NT312.1
unnamed: J601.0, R604.2
unnamed: J702.0 (PAD), R701.1
unnamed: J801.13 (SHIELD), R812.1
unnamed: J801.L1 (LEDY_A), R810.2
unnamed: J801.L4 (LEDG_A), R811.2
unnamed: J801.R1 (TD+), R804.1, U801.20 (TPOUT+)
unnamed: J801.R2 (TD-), R805.2, U801.21 (TPOUT-)
unnamed: J801.R3 (RD+), R806.1, U801.16 (TPIN+)
unnamed: J801.R6 (RD-), R807.2, U801.17 (TPIN-)
unnamed: J1306.1, R1310.2, R1311.2
unnamed: J1306.2, Q1302.3 (D)
unnamed: J1307.1, R1313.2, R1316.2
unnamed: J1307.2, Q1303.3 (D)
unnamed: JP1301.2 (B), R1305.1, U1301.31 (BOOT0)
unnamed: Q401.1 (B), R401.1
unnamed: Q401.3 (C), R402.2
unnamed: Q403.1 (B), R402.1
unnamed: Q403.3 (C), R404.1, R405.2
unnamed: Q1301.1 (B), R1306.2
unnamed: R201.2, U201.22 (MODE)
unnamed: R202.2, U201.21 (~CS)
unnamed: R501.1, U501.14 (SO)
unnamed: R601.2, U601.8 (CH1_OUT)
unnamed: R602.2, U601.7 (CH2_OUT)
unnamed: R603.2, U601.6 (CH3_OUT)
unnamed: R802.1, U801.11 (RBIAS)
unnamed: R803.1, U801.2 (OSC2)
unnamed: R810.1, U801.9 (LEDB)
unnamed: R811.1, U801.10 (LEDA)
unnamed: R902.2, U902.17 (~EXT_RST)
unnamed: R903.2, U902.19 (~BUS_PWR)
unnamed: R904.2, U902.18 (VBUS_SENSE)
unnamed: R905.2, U902.27 (SDA/~TEST)
unnamed: R906.1, U902.14 (REXT)
unnamed: R907.1, U902.22 (LED_CTL/CHRGEN)
unnamed: R908.2, U902.26 (~OVC), U903.4 (~FAULT), U904.4 (~FAULT), U905.4 (~FAULT), U906.4 (~FAULT)
unnamed: R1001.2, R1002.1, R1003.2
unnamed: R1003.1, R1004.2, R1005.2
unnamed: R1005.1, R1006.2, R1007.2
unnamed: R1007.1, R1008.2, R1009.2
unnamed: R1101.2, R1102.1, R1103.2
unnamed: R1103.1, R1104.2, R1105.2
unnamed: R1105.1, R1106.2, R1107.2
unnamed: R1107.1, R1108.2, R1109.2
unnamed: R1201.2, R1202.1, R1203.2
unnamed: R1203.1, R1204.2, R1205.2
unnamed: R1205.1, R1206.2, R1207.2
unnamed: R1207.1, R1208.2, R1209.2
unnamed: R1317.2, R1318.1
unnamed: U902.25 (~PWR), U903.3 (~EN), U904.3 (~EN), U905.3 (~EN), U906.3 (~EN)
VDC: C402.1, C404.2, L401.2, Q403.2 (E), U401.2 (Vin), U402.2 (VIN)

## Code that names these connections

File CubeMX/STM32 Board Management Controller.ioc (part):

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PA6.Mode=Full_Duplex_Slave
Mcu.UserName=STM32F030K6Tx
PA14.GPIO_Label=SWD_CLK
PA0.GPIO_Label=MON_3V3
PA12.GPIOParameters=GPIO_Label
PA9.GPIOParameters=GPIO_Label
PA11.GPIOParameters=GPIO_Label
PA11.Mode=CTS_RTS
PA3.GPIOParameters=GPIO_Label
PA6.GPIO_Label=SPI_CIPO
PB0.GPIO_Label=LED0
PB6.GPIO_Label=I2C_SCL
PA2.GPIOParameters=GPIO_Label
PB5.GPIOParameters=GPIO_Label
PA15.GPIO_Label=PS2_CLK0
PB4.GPIOParameters=GPIO_Label
PA12.Signal=USART1_RTS
PA4.Mode=NSS_Signal_Hard_Input
PB6.Signal=I2C1_SCL
PB6.Mode=I2C
PA8.GPIOParameters=GPIO_Label
PF0-OSC_IN.GPIO_Label=nBUTTON_PWR
PB0.GPIOParameters=GPIO_Label
PA1.GPIOParameters=GPIO_Label
PA14.Mode=Serial_Wire
PB1.GPIO_Label=LED1
PA10.GPIO_Label=UART_RX
PA0.Mode=IN0
PB3.GPIOParameters=GPIO_Label
PB7.Signal=I2C1_SDA
PA8.Signal=GPIO_Output
PB6.GPIOParameters=GPIO_Label
PA0.Signal=ADC_IN0
PA13.GPIOParameters=GPIO_Label
PB7.GPIO_Label=I2C_SDA
Mcu.Package=LQFP32
PB1.Signal=S_TIM3_CH4
PA6.Signal=SPI1_MISO
PA2.GPIO_Label=nSYS_RESET
PA10.Signal=USART1_RX
PA15.Signal=GPXTI15
PA5.GPIOParameters=GPIO_Label
PB5.GPIO_Label=PS2_DAT1
PA4.GPIO_Label=nSPI_CS
PF1-OSC_OUT.Signal=GPIO_Input
PB4.Signal=GPIO_Input
PA3.Signal=GPIO_Output
PA5.Mode=Full_Duplex_Slave
PB3.GPIO_Label=PS2_CLK1
PA6.GPIOParameters=GPIO_Label
PA7.Mode=Full_Duplex_Slave
PA15.GPIOParameters=GPIO_Label
PA10.Mode=Asynchronous
PA9.GPIO_Label=UART_TX
PA11.GPIO_Label=UART_CTS
PA12.GPIO_Label=UART_RTS
PA13.Signal=SYS_SWDIO
PA9.Mode=Asynchronous
PA8.GPIO_Label=nHOST_IRQ
PB7.GPIOParameters=GPIO_Label
PA9.Signal=USART1_TX
PF1-OSC_OUT.GPIOParameters=GPIO_Label
PA1.Signal=ADC_IN1
PA5.Signal=SPI1_SCK
board=custom
PA1.Mode=IN1
PB4.GPIO_Label=PS2_DAT0
PA1.GPIO_Label=MON_5V0
PF1-OSC_OUT.GPIO_Label=nBUTTON_RST
PA10.GPIOParameters=GPIO_Label
PA4.GPIOParameters=GPIO_Label
PA13.Mode=Serial_Wire
Mcu.Name=STM32F030K6Tx
PA2.Signal=GPIO_Output
PA13.GPIO_Label=SWD_IO
PB3.Signal=GPXTI3
PA4.Signal=SPI1_NSS
PB5.Signal=GPIO_Input
PA7.GPIO_Label=SPI_COPI
PA12.Mode=CTS_RTS
PA5.GPIO_Label=SLK_CLK
PA14.GPIOParameters=GPIO_Label
PB7.Mode=I2C
PA11.Signal=USART1_CTS
PA14.Signal=SYS_SWCLK
PA0.GPIOParameters=GPIO_Label
PF0-OSC_IN.Signal=GPIO_Input
PF0-OSC_IN.GPIOParameters=GPIO_Label
PB0.Signal=S_TIM3_CH3
PA7.GPIOParameters=GPIO_Label
PA3.GPIO_Label=DC_ON
PB1.GPIOParameters=GPIO_Label
PA7.Signal=SPI1_MOSI

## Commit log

2020-12-05 Adding a skeleton ATX board layout to demonstrate connector layout.
2020-12-13 Add some comments to the schematic.
2020-12-13 Added 3D models for all edge connectors.
    Also moved down a directory to make it simpler.
2020-12-14 Add some more components to the library.
2020-12-14 Update notes on schematic.
2020-12-17 Fixing up hole locations on the PCB.
2020-12-20 Splitting into sub-modules.
    Also started Audio jack connections.
2020-12-20 Completed Audio sheet.
2020-12-20 Trying out a new action file.
2020-12-20 Remove empty action file
2020-12-20 Test commit
2020-12-20 Dummy change
2020-12-20 Specifying full path.
    Also add git attributes and git config.
2020-12-20 Need to touch an sch to get it to build.
2020-12-20 Ignore docs folder
2020-12-20 Describe schematic sections in README and start changelog.
2020-12-20 Ignore project backup files
2020-12-20 Brought in RS232 circuit from Neotron 32.
    Also updated 3D models.
2020-12-20 No SVG schematics.
2020-12-22 Tidied up Audio page.
2020-12-22 Updating BOM with parts.
2020-12-22 Updated audio sheet.
2020-12-22 Wired up Ethernet sheet.
2020-12-22 Gave sheets unique titles
2020-12-22 Add ATX/ITX mounting holes.
2020-12-22 Add logos
2020-12-23 Added dual Type-A USB header.
2020-12-24 Working on VGA sheet and USB sheet.
    Also added courtyard and silk to stacked USB connector.
2020-12-25 Make sure we run ERC.
    Also clean out comments - we can refer back to the docs for these.
2020-12-25 Set revision to [Uncontrolled]
2020-12-25 Fix up ERC errors.
    ~FAULT on the MIC2005 is an active-low common collector output.
    Well done ERC for spotting that I can't join three output pins together!
2020-12-25 Update README - no DAC, and note we have current limiters on USB
2020-12-25 Add master USB power switch.
2020-12-25 Added empty SD card sheet.
2020-12-26 Set one of the AP2501 power output pins as passive.
    Otherwise the ERC complains we have two power outputs connect to each
    other.
2020-12-26 Re-run docs on lib change.
2020-12-26 Re-run docs on footprint change.
2020-12-26 Script for making a github release.
    From https://github.com/actions/upload-release-asset
2020-12-26 Remove duplicate name
2020-12-26 Need to create zip file recursively.
    Also put tag name in asset.
2020-12-26 OK, so you can't put the tag name in the filename.
    This is because the tag starts `refs/tags/`
2020-12-26 Set version number in Kicad files.
2020-12-26 Use github ref - git describe doesn't seem to work.
2020-12-26 Remove refs/tags
2020-12-26 Added SD card sheet.
    Simple setup - 10k pullups, no ESD protection.
2020-12-26 Replace licence text with correct CC BY-SA 4.0 International text.
2020-12-26 Update Changelog
2020-12-26 Fix V+ capacitor - must go to ground, not Vcc.
2020-12-26 Completed PSU design.
    Also changed footprint for stacked USB connector to change
    shield pins from SHx to Pin 9.
2020-12-27 Replaced NUC029 (TSSOP) with KE04 (SOIC).
    Also updated the BOM with some part nos.
2020-12-27 Updated PCB
2020-12-29 Added CPU socket.
2020-12-29 Video sheet takes digital video, not analog video.
    DAC is TBD.
2020-12-29 Make CPU card bigger.
    Just big enough to take a TQFP-176 now.
2020-12-30 Revised CPU connector to be two 2x20.
    This gives more room for larger TQFP-176+ CPUs to be fitted that
    didn't fit on the PGA-80 design.
2020-12-30 Changed CPU socket to be 2x20 x2. Added expansion slots.
    Also added 3D model for the SD card.
2020-12-31 Rejigged expansion socket, and added pinout to README.
2020-12-31 Updated changelog.
2021-01-01 Add real-time clock.
    I copied the MCP7940N design from the Neotron-32 but changed
    the chip to a SOIC-8.
2021-01-01 Bring in R2R DAC from Neotron-9X schematic.
2021-01-01 Remove old "mpn" field on components.
    Use "MPN" instead.
2021-01-01 Updated Changelog
2021-01-01 Fix ERC error when CIPO pins joined together.
    Tristate the CIPO pin on an expansion slot, and on the Ethernet chip.
2021-01-01 Update Changelog.
2021-01-01 Added some part numbers.
2021-01-01 Marked no-fit parts
2021-01-01 Updated PCB with latest netlist.
2021-01-06 Replaced KE04Z with STM32F0.
    Had trouble debugging a test KE06Z device. Decided an STM32 would be simpler.
2021-01-07 Updating part nos.
2021-01-07 Tweaking some 3D models.
2021-01-07 Update README.md
    Added arrows to CPU header diagram
    Added suggestions for future expansion cards
    Specified EEPROM addresses for each slot
    Clarified types of regulator used
    Noted that BMC runs from standby regulator
    Note that internal line-in doesn't work if external line-in used (but line-output does work if headphone out is used)
2021-01-07 Swap row and column in README for CPU pinout
2021-01-07 Swap pinout on CPU connector to better match SDMMC connector.
2021-01-08 Switch to 8 pin debug header (J902)
    Closes #15
2021-01-08 K7805-3AR3 updates:
    ) Add footprint with courtyard.
    ) Note that several of the pins are duplicated, not independent.
    ) Add aliases for other voltage variants.
    ) Tidy up schematic back on to the 50 mil grid.
2021-01-08 Add 3D models to USB header.
2021-01-08 Add 2.54mm header for case LED.
2021-01-08 Remove Mouser fields where not set.
2021-01-08 Change ST to ST Micro for consistency
2021-01-08 Updated PCB from Schematic.
2021-01-08 Replace inductor with horizontal footprint.
2021-01-08 Update CHANGELOG with release.
    Also fix typo in README about input voltage range.
2021-01-16 Switch some of the radial THT Electrolytic caps for SMD MLCCs.
    Also changed the STM32 for an LQFP-32 as it has a bigger pitch on the
    pins.
    The LQFP is easier to solder than the TSSOP, and the MLCC takes are
    cheaper and take up less space.
2021-01-18 Update 4u7 cap to 16V
2021-03-29 README updates.
    Correct part number for STM32 BMC.
    Added footprints to README, and other details.
2021-03-29 Updated CHANGELOG for 0.8.0
2021-03-31 This pinout should match more STM32 devices.
    Schematic still needs updating.
2021-04-02 Added 12-bit video DAC.
    Also had to change footprints to suit Kicad 5.1.9
2021-04-02 Add 4-bit Video DAC, and re-wire BMC.
    Now the BMC is an SPI device, and has a four-wire UART.
2021-04-02 Tidy up part nos and swapped I2C/UART on BMC.
    Mark all resistors as 1% if not specified.
    Added some Mouser part numbers.
    BMC can now be programmed over UART.
2021-04-02 Add git clean/smudge commands to README
2021-04-04 Changes to BMC
    * Swapped BUTTON_PWR and SYS_RESET to avoid DRC issue
    * Split PSU and BMC into two separate sheets
    * Swapped some pins on the STM32 to make it compatible with more
    alternatives
2021-04-04 Set LR and BCLK on Audio.sch to be bi-directional
    In Controller mode these pins are outputs. In peripheral
    mode these pins are inputs.
2021-04-05 Join GNDA and GND on audio sheet.
    Most guides recommend against having a split ground, and it certainly
    makes layout harder.
2021-04-06 Revised PSU switch-on circuit.
    Updated notes on BMC and Audio sheet.
2021-04-06 Fix spaces in MPNs.
2021-04-06 Remove more errant spaces.
2021-06-18 Brought in sheets from Neotron Pico.
    Also includes DB15HD and PSU 3D models.
2021-06-18 Merge in more changes.
    Mostly lowering voltage tolerances to minimum required.
2021-06-18 Fixups after last copy-over.
2021-06-18 Run GHA.
    Copied from Neotron Pico.
2021-06-18 Disable PCB checks - we don't have a PCB in this project.
    Just a collection of parts which are not tracked, just dumped on the board.
2021-08-07 Add second variant of TPF133a with pins swapped around.
    Might make PCB layout easier. Channels are interchangeble.
2021-08-18 Added expansion edge footprint and matching symbol.
2021-08-18 Update README and CHANGELOG.
2021-08-20 Rename THS7316_copy to THS7316-swap
2022-12-24 Update fileformats to Kicad 6.
2022-12-24 Update kibot from Neotron Pico
2022-12-24 Update schematic files to Kicad 6.
    Had to fix some symbols which didn't have perfect matches in K6.
2022-12-24 Fixup PCB.
    We don't run DRC as the PCB isn't routed.
2022-12-24 Imported sheets from Neotron Pico.
    Standardised on +3V3 not +3.3V
2022-12-24 UNIX cares about case sensitivity
2022-12-24 Actions have DRC and ERC backwards.
2022-12-24 Set missing footprints and update PCB
2022-12-26 Re-imported from Neotron Pico v1.1.
    This time I deleted the sheets from the top level and then re-added pointing at the new files. I also reset the PCB dimensions to match the Neotron Pico.
    This seems to have done a better job importing footprints.
2023-02-20 Adjusted K78XX-3AR3.kicad_mod footprint to reflect dimensions of Pi Pico through hole dimensions (1.7mm x 1.02mm)
2023-04-01 Update to KiCAD 7
2023-04-01 Update CI to use KiCAD 7 container
2023-04-01 Mark SD Card slot as SMD.
    Removes warning using KiCAD 7.
2023-04-01 Docs updates
2023-04-06 Update date/versions/copryright.
2023-04-06 Update PCB metadata.

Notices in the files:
Kicad/Neotron-Common-Hardware.kicad_pcb:
Licenced as CC BY-SA
Copyright (c) The Neotron Developers, 2023
